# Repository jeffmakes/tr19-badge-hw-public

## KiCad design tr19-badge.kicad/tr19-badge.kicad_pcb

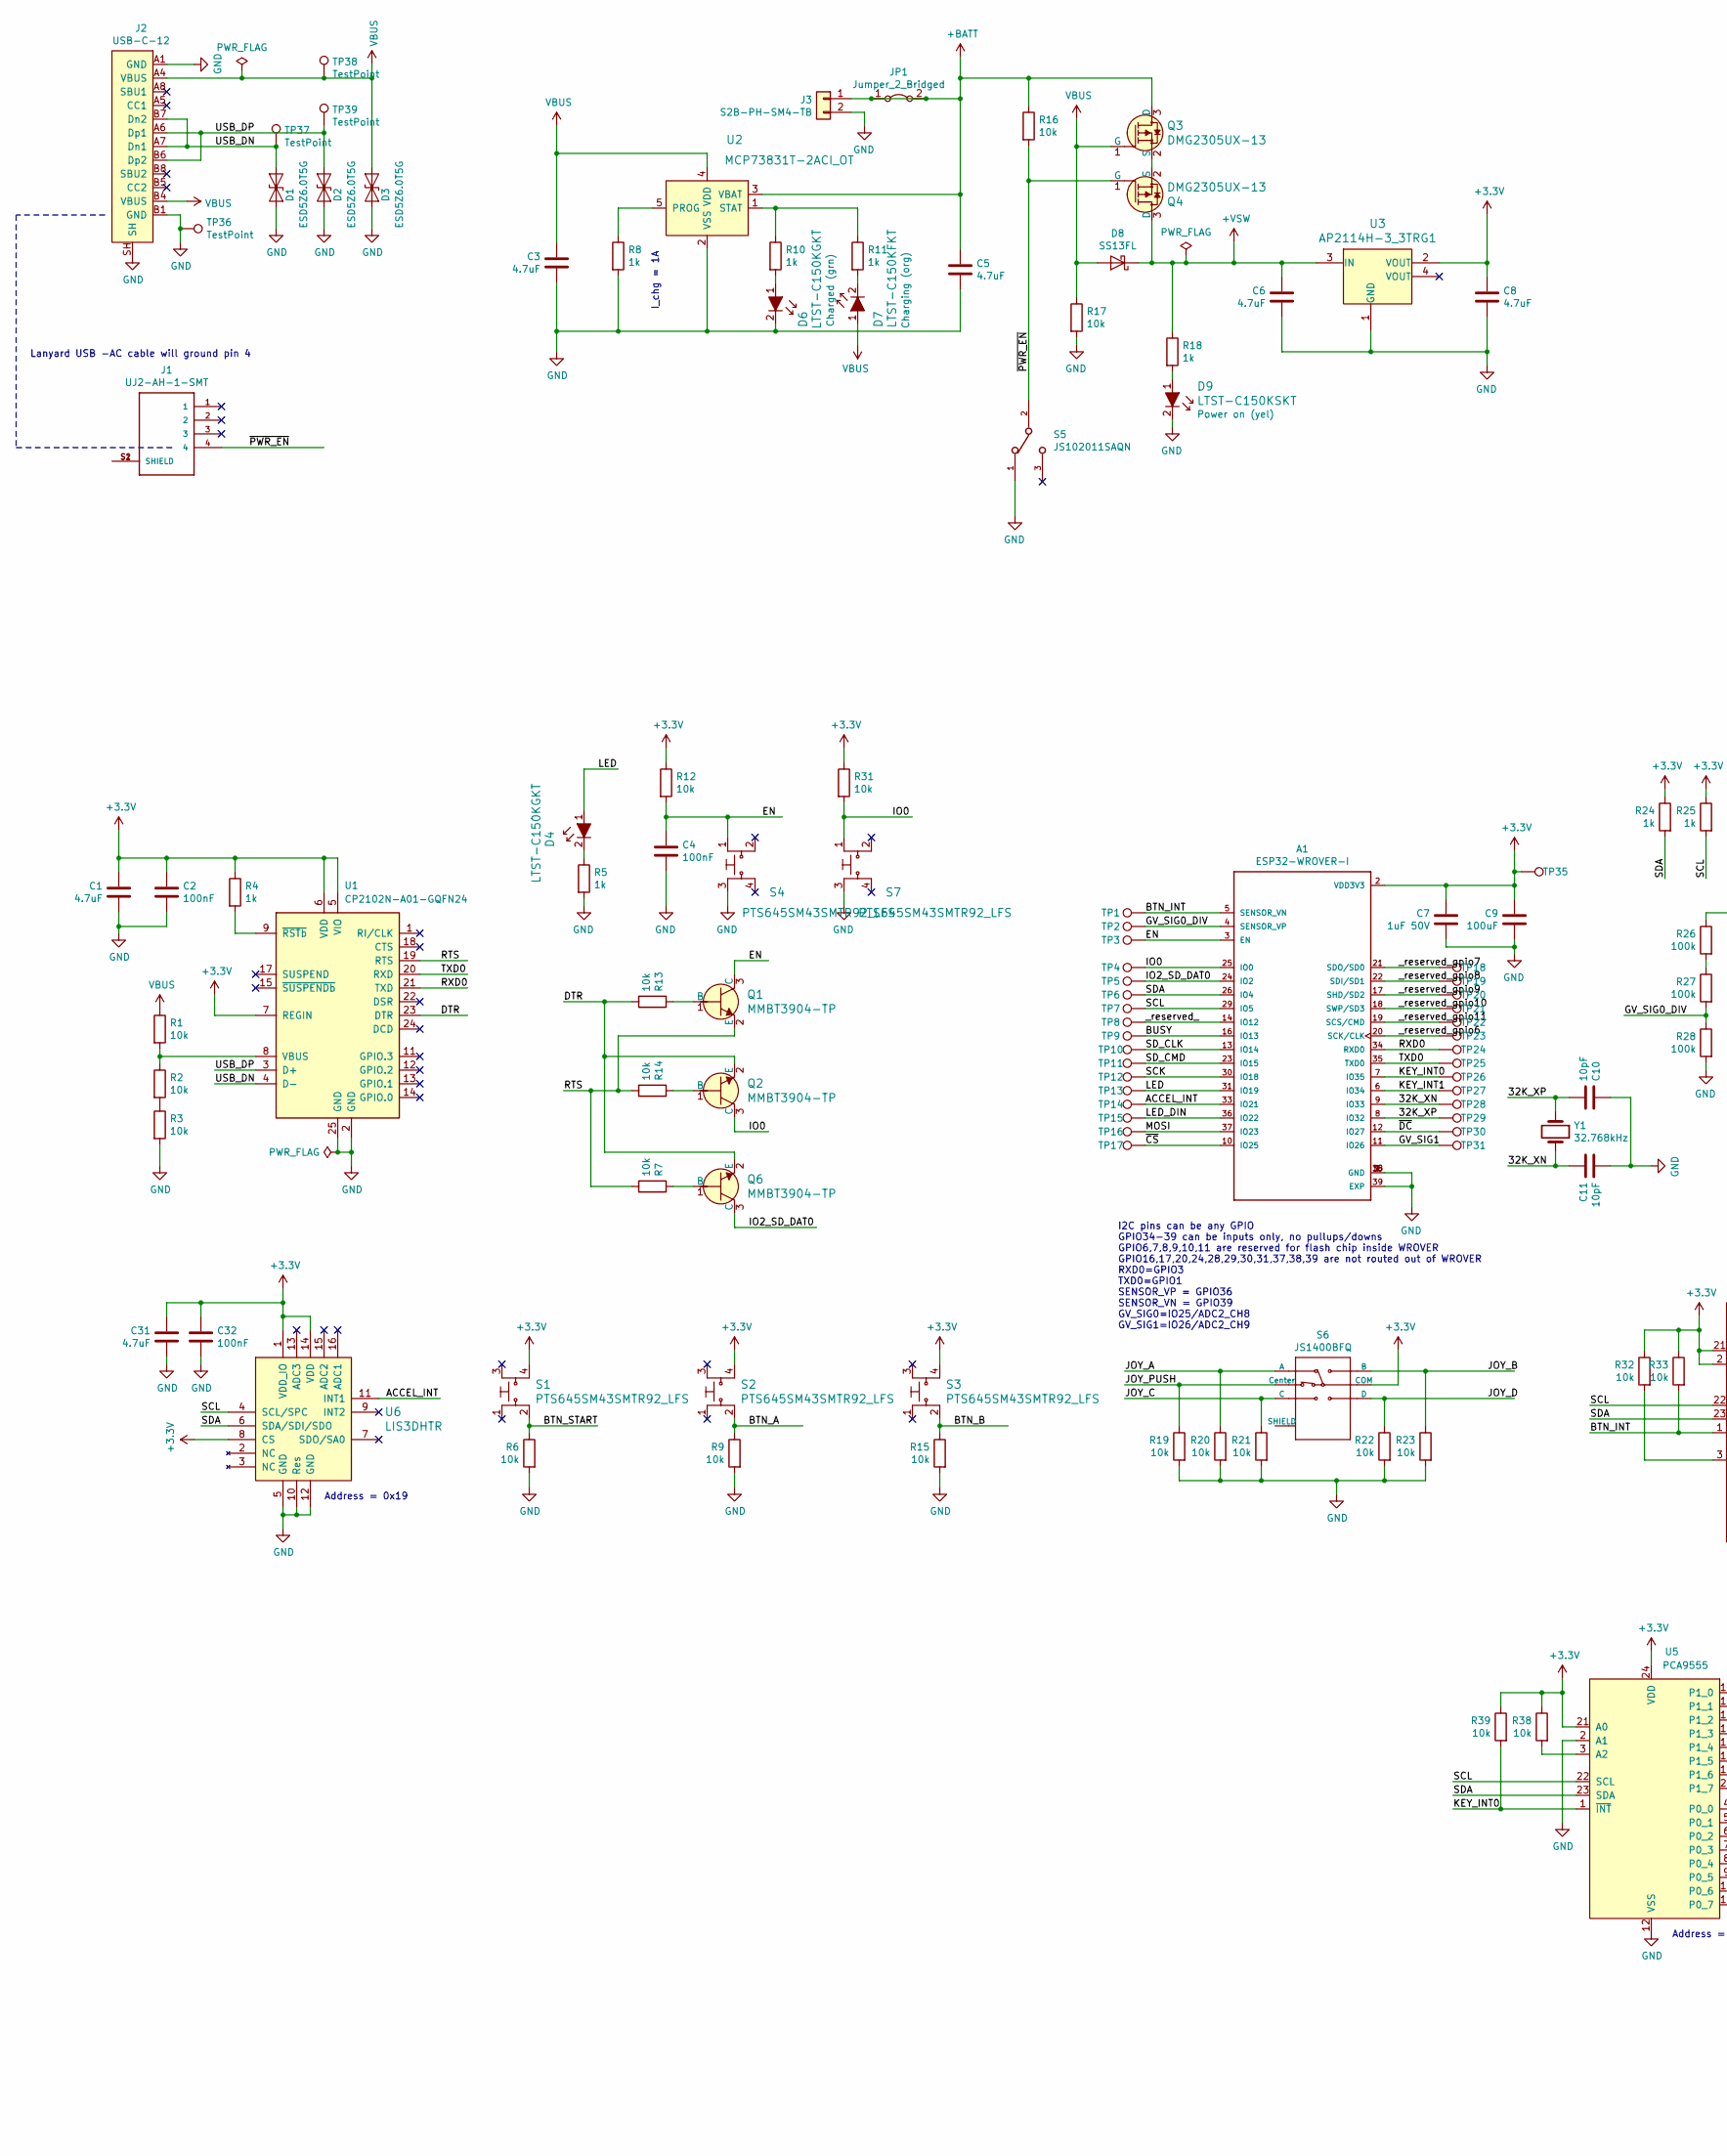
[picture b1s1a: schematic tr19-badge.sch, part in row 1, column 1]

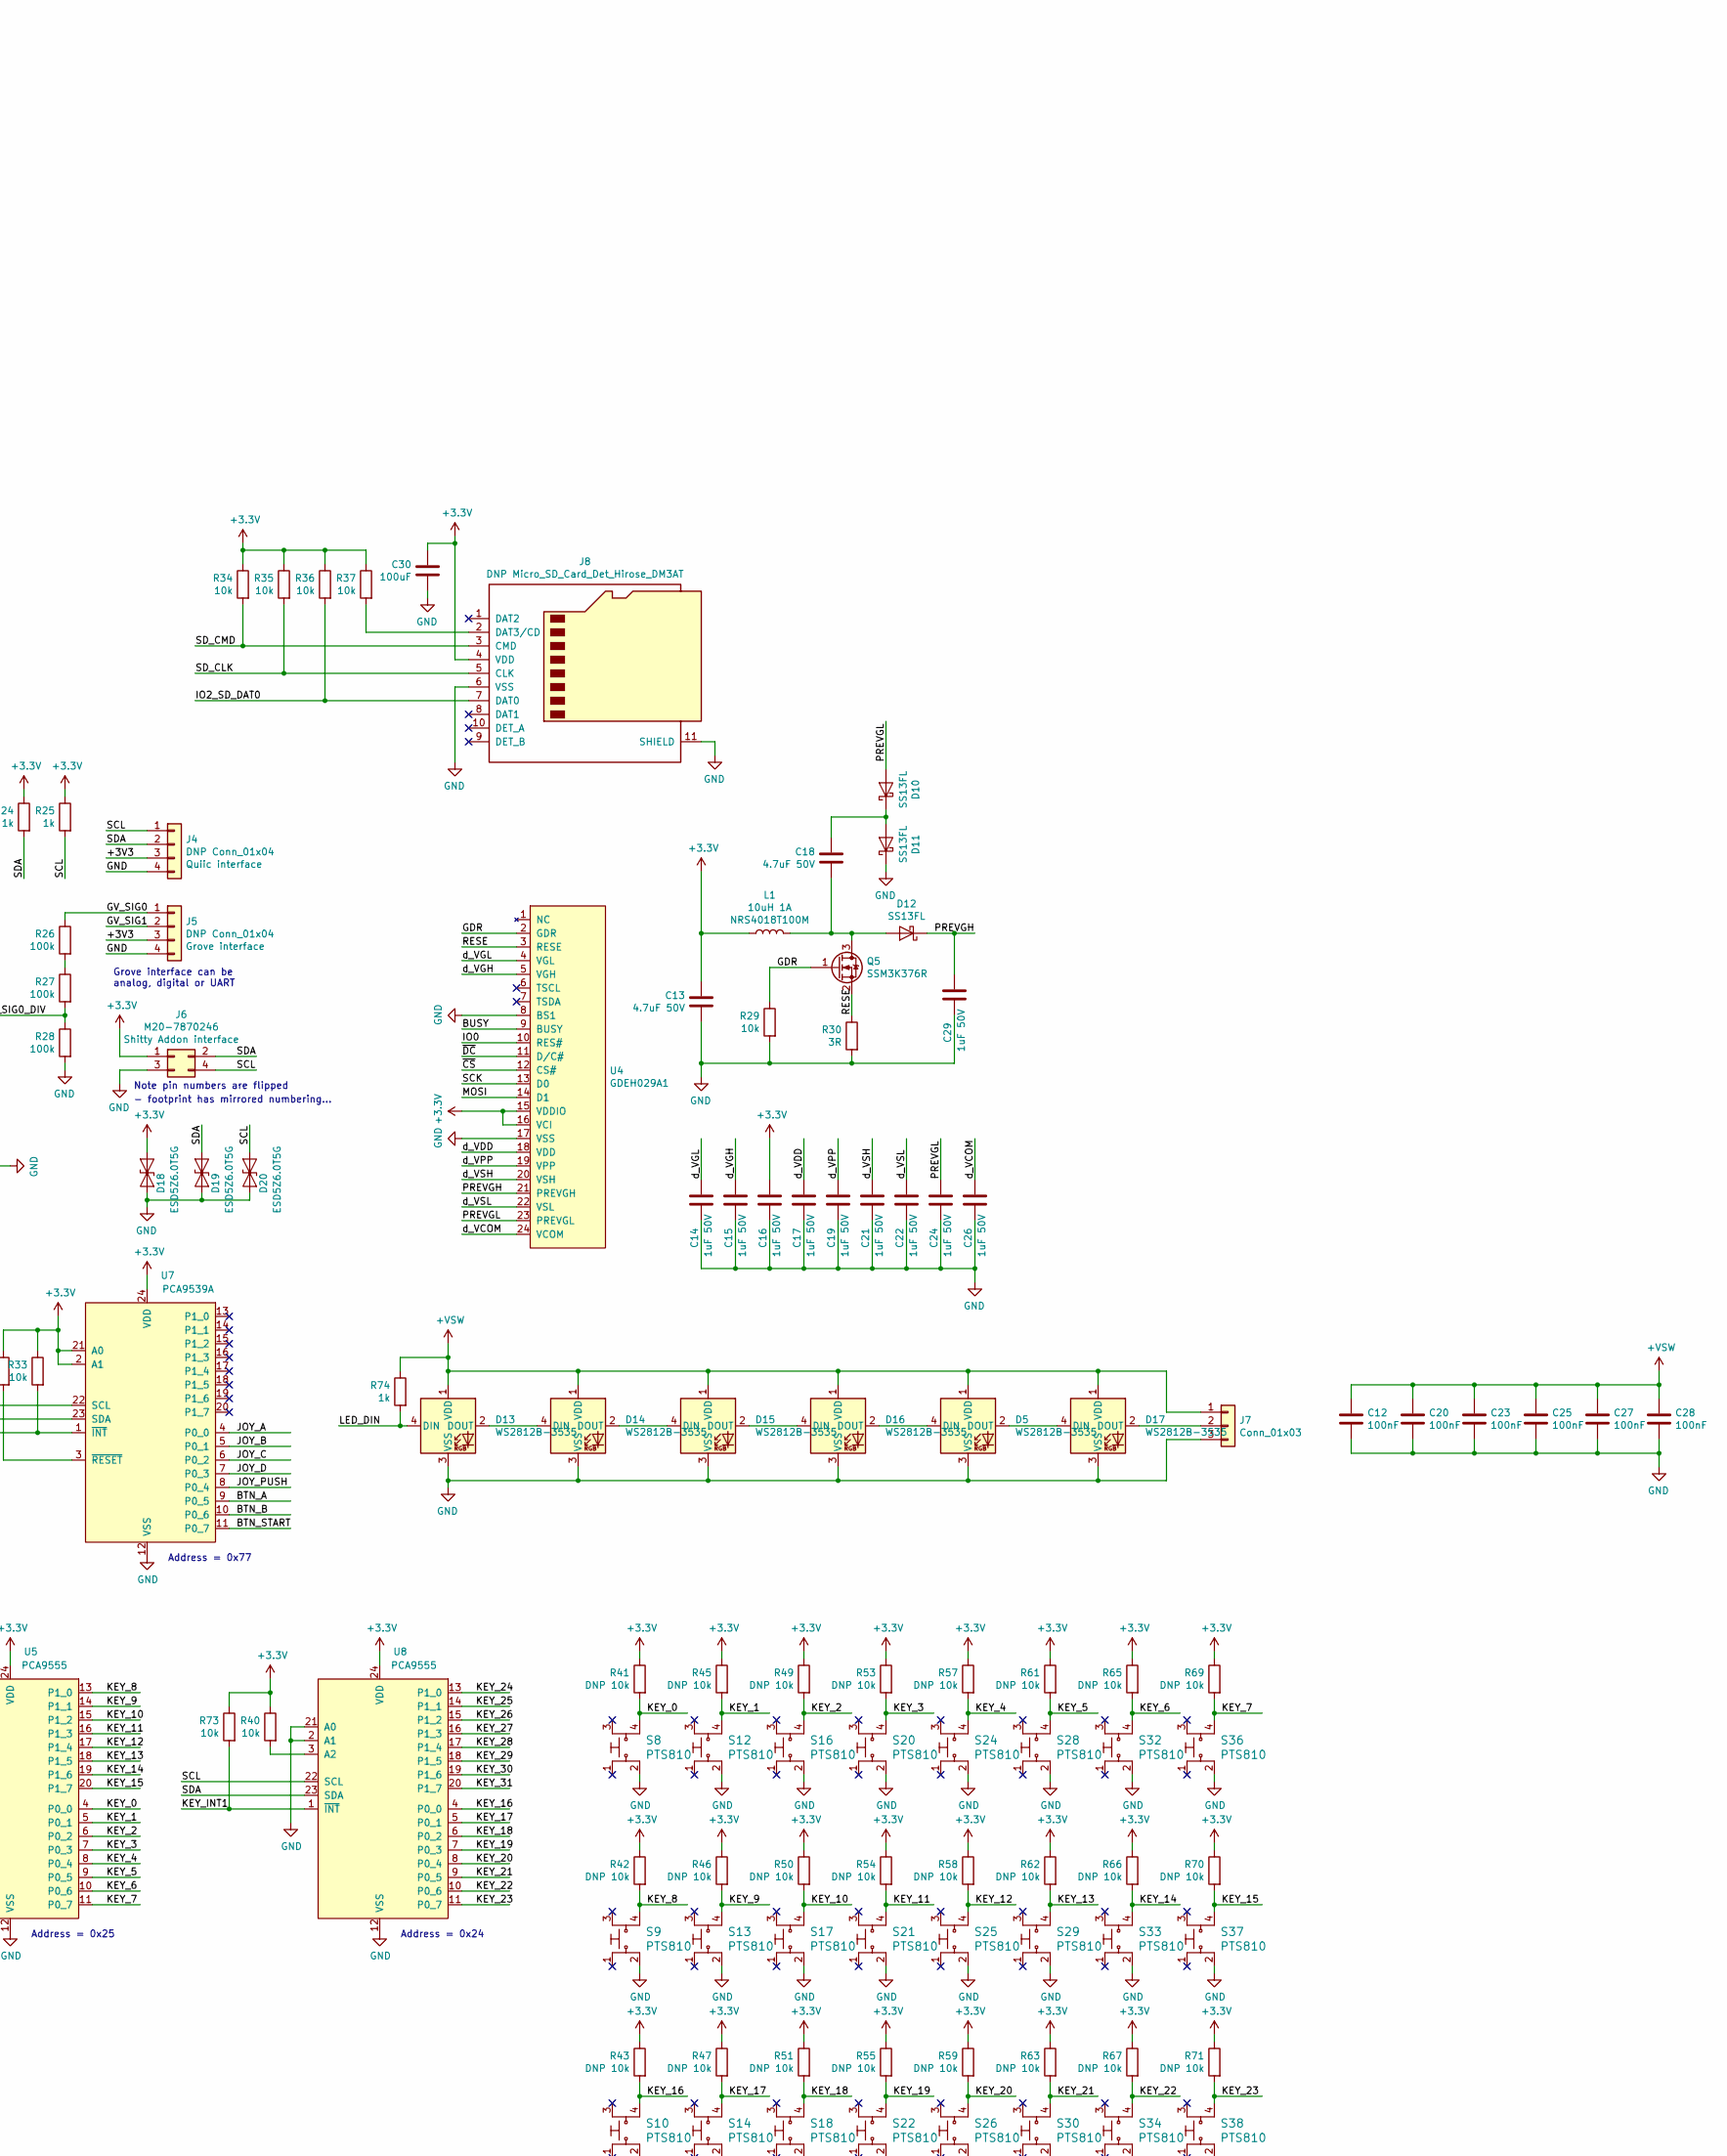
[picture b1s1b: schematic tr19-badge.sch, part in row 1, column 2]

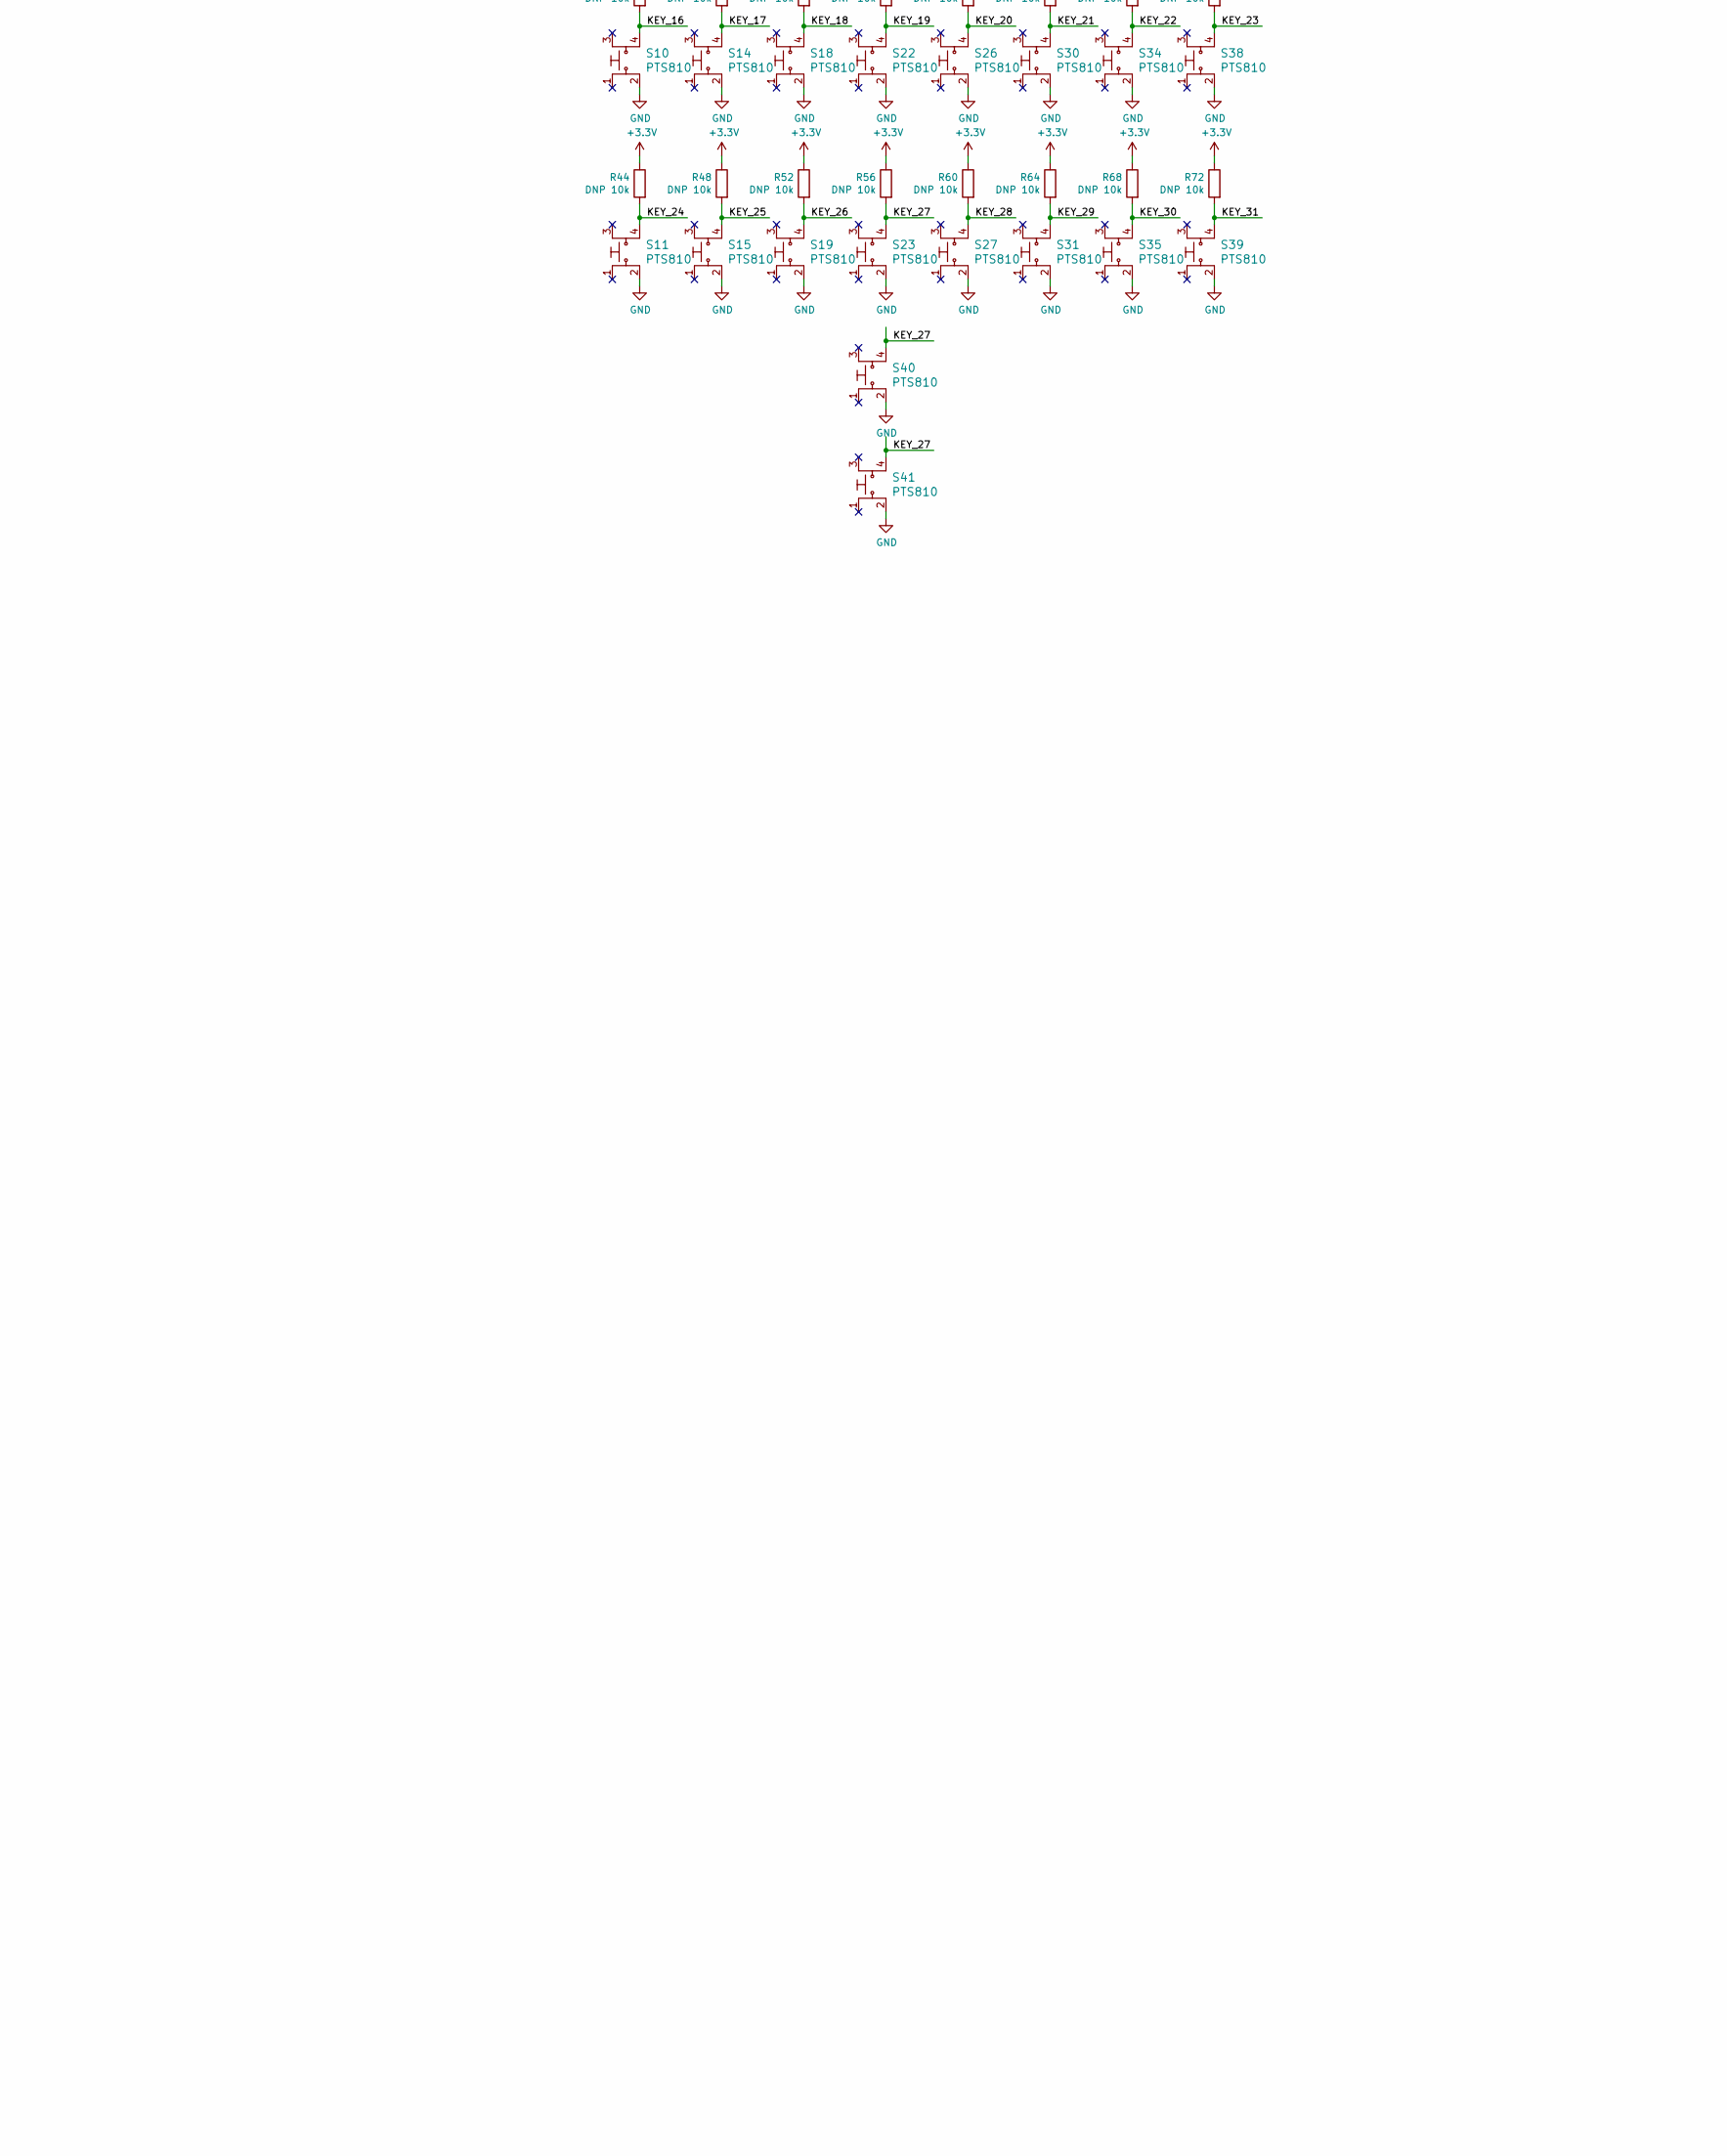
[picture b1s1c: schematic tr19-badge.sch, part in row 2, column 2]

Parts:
A1: ESP32-WROVER-I
C1, C3, C5, C6, C8, C31: 4.7uF; C_0603_1608Metric
C2, C4, C12, C20, C23, C25, C27, C28, C32: 100nF; C_0603_1608Metric
C7, C14, C15, C16, C17, C19, C21, C22, C24, C26, C29: 1uF 50V; C_0805_2012Metric
C9, C30: 100uF; C_1210_3225Metric
C10, C11: 10pF; C_0603_1608Metric
C13, C18: 4.7uF 50V; C_0805_2012Metric
D1, D2, D3, D18, D19, D20: ESD5Z6.0T5G; SOD-523-numbered-pads; MPN ESD5Z5.0VC
D4, D6: LTST-C150KGKT; 1206; MPN LTST-C150KGKT; Digi-Key_PN 160-1404-1-ND
D5, D13, D14, D15, D16, D17: WS2812B-3535; LED_SK6812MINI_PLCC4_3.5x3.5mm_P1.75mm_no_silk
D7: LTST-C150KFKT; 1206; MPN LTST-C150KSKT; Digi-Key_PN 160-1406-1-ND
D8, D10, D11, D12: SS13FL; D_SOD-123F
D9: LTST-C150KSKT; 1206; MPN LTST-C150KSKT; Digi-Key_PN 160-1406-1-ND
J1: UJ2-AH-1-SMT; jing-lcsc-C46400
J2: USB-C-12; jing-usb-c-lcsc-C167321
J3: S2B-PH-SM4-TB; JST_PH_S2B-PH-SM4-TB_1x02-1MP_P2.00mm_Horizontal
J4: DNP Conn_01x04; JST_SH_SM04B-SRSS-TB_1x04-1MP_P1.00mm_Horizontal
J5: DNP Conn_01x04; 1125R-SMT-4P
J6: M20-7870246; PinSocket_2x02_P2.54mm_Vertical_mirror_numbering
J7: Conn_01x03; PinHeader_1x03_P2.54mm_Vertical
J8: DNP Micro_SD_Card_Det_Hirose_DM3AT; microSD_HC_Hirose_DM3AT-SF-PEJM5
JP1: Jumper_2_Bridged; PinHeader_1x02_P2.54mm_Vertical
L1: 10uH 1A; L_Taiyo-Yuden_MD-5050; MPN NRS4018T100M
Q1, Q2, Q6: MMBT3904-TP; SOT-23-3; MPN MMBT3904-TP; Digi-Key_PN MMBT3904TPMSCT-ND
Q3, Q4: DMG2305UX-13; SOT-23-3; MPN DMG2305UX-13; Digi-Key_PN DMG2305UX-13DICT-ND
Q5: SSM3K376R; SOT-23
R1, R2, R3, R6, R7, R9, R12, R13, R14, R15, R16, R17, R19, R20, R21, R22, R23, R29, R31, R32, R33, R34, R35, R36, R37, R38, R39, R40, R73: 10k; R_0603_1608Metric
R4, R5, R8, R10, R11, R18, R24, R25, R74: 1k; R_0603_1608Metric
R26, R27, R28: 100k; R_0603_1608Metric
R30: 3R; R_0603_1608Metric
R41, R42, R43, R44, R45, R46, R47, R48, R49, R50, R51, R52, R53, R54, R55, R56, R57, R58, R59, R60, R61, R62, R63, R64, R65, R66, R67, R68, R69, R70, R71, R72: DNP 10k; R_0603_1608Metric
S1, S2, S3, S4, S7: PTS645SM43SMTR92_LFS; Switch_Tactile_SMD_6x6mm_PTS645; MPN PTS645SM43SMTR92 LFS; Digi-Key_PN CKN9112CT-ND
S5: JS102011SAQN; SW_JS102011SAQN
S6: JS1400BFQ; SW_JS1400BFQ-arrows
S8, S9, S10, S11, S12, S13, S14, S15, S16, S17, S18, S19, S20, S21, S22, S23, S24, S25, S26, S27, S28, S29, S30, S31, S32, S33, S34, S35, S36, S37, S38, S39, S40, S41: PTS810; PTS-810; MPN PTS645SM43SMTR92 LFS; Digi-Key_PN CKN9112CT-ND
TP1, TP2, TP3, TP4, TP5, TP6, TP7, TP8, TP9, TP10, TP11, TP12, TP13, TP14, TP15, TP16, TP17, TP18, TP19, TP20, TP21, TP22, TP23, TP24, TP25, TP26, TP27, TP28, TP29, TP30, TP31, TP35: test-pad-1.4-TH
TP36, TP37, TP38, TP39: TestPoint; test-pad-1.4-TH
U1: CP2102N-A01-GQFN24; QFN-24-1EP_4x4mm_P0.5mm_EP2.6x2.6mm
U2: MCP73831T-2ACI_OT; SOT-753; MPN MCP73831T-2ACI/OT; Digi-Key_PN MCP73831T-2ACI/OTCT-ND
U3: AP2114H-3_3TRG1; SOT-223; MPN AP2114H-3.3TRG1; Digi-Key_PN AP2114H-3.3TRG1DICT-ND
U4: GDEH029A1
U5, U8: PCA9555; TSSOP-24_4.4x7.8mm_P0.65mm
U6: LIS3DHTR; VFLGA-16_3x3mm; MPN LIS3DHTR; Digi-Key_PN 497-10613-1-ND
U7: PCA9539A; TSSOP-24_4.4x7.8mm_P0.65mm
Y1: 32.768kHz; Crystal_SMD_3215-2Pin_3.2x1.5mm; MPN SSP-T7-F

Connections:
+BATT: C5.1, J3.1, JP1.1 (A), JP1.2 (B), Q3.3 (D), R16.1, U2.3 (VBAT)
+VSW: C6.1, C12.1, C20.1, C23.1, C25.1, C27.1, C28.1, D5.1 (VDD), D8.1 (K), D13.1 (VDD), D14.1 (VDD), D15.1 (VDD), D16.1 (VDD), D17.1 (VDD), J7.1, Q4.3 (D), R18.1, R74.1, U3.3 (IN)
/32K_XN: A1.9 (IO33), C11.1, TP28.1, Y1.2
/32K_XP: A1.8 (IO32), C10.2, TP29.1, Y1.1
/ACCEL_INT: A1.33 (IO21), TP14.1, U6.11 (INT1)
/BTN_A: R9.1, S2.2, U7.9 (P0_5)
/BTN_B: R15.1, S3.2, U7.10 (P0_6)
/BTN_INT: A1.5 (SENSOR_VN), R33.2, TP1.1, U7.1 (~INT~)
/BTN_START: R6.1, S1.2, U7.11 (P0_7)
/BUSY: A1.16 (IO13), TP9.1, U4.9 (BUSY)
/DTR: Q2.2 (E), Q6.2 (E), R13.2, U1.23 (DTR)
/EN: A1.3 (EN), C4.1, Q1.3 (C), R12.2, S4.1, TP3.1
/GDR: Q5.1 (G), R29.1, U4.2 (GDR)
/GV_SIG0: J5.1, R26.1
/GV_SIG0_DIV: A1.4 (SENSOR_VP), R27.2, R28.1, TP2.1
/GV_SIG1: A1.11 (IO26), J5.2, TP31.1
/IO0: A1.25 (IO0), Q2.3 (C), R31.2, S7.1, TP4.1, U4.10 (RES#)
/IO2_SD_DAT0: A1.24 (IO2), J8.7 (DAT0), Q6.3 (C), R36.2, TP5.1
/JOY_A: R20.1, S6.1 (A), U7.4 (P0_0)
/JOY_B: R23.1, S6.4 (B), U7.5 (P0_1)
/JOY_C: R21.1, S6.3 (C), U7.6 (P0_2)
/JOY_D: R22.1, S6.6 (D), U7.7 (P0_3)
/JOY_PUSH: R19.1, S6.2 (Center), U7.8 (P0_4)
/KEY_0: R41.2, S8.4, U5.4 (P0_0)
/KEY_1: R45.2, S12.4, U5.5 (P0_1)
/KEY_2: R49.2, S16.4, U5.6 (P0_2)
/KEY_3: R53.2, S20.4, U5.7 (P0_3)
/KEY_4: R57.2, S24.4, U5.8 (P0_4)
/KEY_5: R61.2, S28.4, U5.9 (P0_5)
/KEY_6: R65.2, S32.4, U5.10 (P0_6)
/KEY_7: R69.2, S36.4, U5.11 (P0_7)
/KEY_8: R42.2, S9.4, U5.13 (P1_0)
/KEY_9: R46.2, S13.4, U5.14 (P1_1)
/KEY_10: R50.2, S17.4, U5.15 (P1_2)
/KEY_11: R54.2, S21.4, U5.16 (P1_3)
/KEY_12: R58.2, S25.4, U5.17 (P1_4)
/KEY_13: R62.2, S29.4, U5.18 (P1_5)
/KEY_14: R66.2, S33.4, U5.19 (P1_6)
/KEY_15: R70.2, S37.4, U5.20 (P1_7)
/KEY_16: R43.2, S10.4, U8.4 (P0_0)
/KEY_17: R47.2, S14.4, U8.5 (P0_1)
/KEY_18: R51.2, S18.4, U8.6 (P0_2)
/KEY_19: R55.2, S22.4, U8.7 (P0_3)
/KEY_20: R59.2, S26.4, U8.8 (P0_4)
/KEY_21: R63.2, S30.4, U8.9 (P0_5)
/KEY_22: R67.2, S34.4, U8.10 (P0_6)
/KEY_23: R71.2, S38.4, U8.11 (P0_7)
/KEY_24: R44.2, S11.4, U8.13 (P1_0)
/KEY_25: R48.2, S15.4, U8.14 (P1_1)
/KEY_26: R52.2, S19.4, U8.15 (P1_2)
/KEY_27: R56.2, S23.4, S40.4, S41.4, U8.16 (P1_3)
/KEY_28: R60.2, S27.4, U8.17 (P1_4)
/KEY_29: R64.2, S31.4, U8.18 (P1_5)
/KEY_30: R68.2, S35.4, U8.19 (P1_6)
/KEY_31: R72.2, S39.4, U8.20 (P1_7)
/KEY_INT0: A1.7 (IO35), R39.2, TP26.1, U5.1 (~INT~)
/KEY_INT1: A1.6 (IO34), R73.2, TP27.1, U8.1 (~INT~)
/LED: A1.31 (IO19), D4.1, TP13.1
/LED_DIN: A1.36 (IO22), D13.4 (DIN), R74.2, TP15.1
/MOSI: A1.37 (IO23), TP16.1, U4.14 (D1)
/PREVGH: C29.2, D12.1 (K), U4.21 (PREVGH)
/PREVGL: C24.2, D10.2 (A), U4.23 (PREVGL)
/RESE: Q5.2 (S), R30.1, U4.3 (RESE)
/RTS: Q1.2 (E), R7.2, R14.2, U1.19 (RTS)
/RXD0: A1.34 (RXD0), TP24.1, U1.21 (TXD)
/SCK: A1.30 (IO18), TP12.1, U4.13 (D0)
/SCL: A1.29 (IO5), D20.1 (A1), J4.1, J6.4, R25.2, TP7.1, U5.22 (SCL), U6.4 (SCL/SPC), U7.22 (SCL), U8.22 (SCL)
/SDA: A1.26 (IO4), D19.1 (A1), J4.2, J6.2, R24.2, TP6.1, U5.23 (SDA), U6.6 (SDA/SDI/SDO), U7.23 (SDA), U8.23 (SDA)
/SD_CLK: A1.13 (IO14), J8.5 (CLK), R35.2, TP10.1
/SD_CMD: A1.23 (IO15), J8.3 (CMD), R34.2, TP11.1
/TXD0: A1.35 (TXD0), TP25.1, U1.20 (RXD)
/USB_DN: D1.1 (A1), J2.A7 (Dn1), J2.B7 (Dn2), TP37.1, U1.4 (D-)
/USB_DP: D2.1 (A1), J2.A6 (Dp1), J2.B6 (Dp2), TP39.1, U1.3 (D+)
/_reserved_: A1.14 (IO12), TP8.1
/_reserved_gpio6: A1.20 (SCK/CLK), TP23.1
/_reserved_gpio7: A1.21 (SDO/SD0), TP18.1
/_reserved_gpio8: A1.22 (SDI/SD1), TP19.1
/_reserved_gpio9: A1.17 (SHD/SD2), TP20.1
/_reserved_gpio10: A1.18 (SWP/SD3), TP21.1
/_reserved_gpio11: A1.19 (SCS/CMD), TP22.1
/d_VCOM: C26.2, U4.24 (VCOM)
/d_VDD: C17.2, U4.18 (VDD)
/d_VGH: C15.2, U4.5 (VGH)
/d_VGL: C14.2, U4.4 (VGL)
/d_VPP: C19.2, U4.19 (VPP)
/d_VSH: C21.2, U4.20 (VSH)
/d_VSL: C22.2, U4.22 (VSL)
/~CS~: A1.10 (IO25), TP17.1, U4.12 (CS#)
/~DC~: A1.12 (IO27), TP30.1, U4.11 (D/C#)
/~PWR_EN~: J1.4, Q4.1 (G), R16.2, S5.2
GND: A1.1 (GND), A1.15 (GND), A1.38 (GND), A1.39 (EXP), C1.2, C2.2, C3.2, C4.2, C5.2, C6.2, C7.2, C8.2, C9.2, C10.1, C11.2, C12.2, C13.2, C14.1, C15.1, C16.1, C17.1, C19.1, C20.2, C21.1, C22.1, C23.2, C24.1, C25.2, C26.1, C27.2, C28.2, C29.1, C30.2, C31.2, C32.2, D1.2 (A2), D2.2 (A2), D3.2 (A2), D5.3 (VSS), D6.2, D9.2, D11.1 (K), D13.3 (VSS), D14.3 (VSS), D15.3 (VSS), D16.3 (VSS), D17.3 (VSS), D18.2 (A2), D19.2 (A2), D20.2 (A2), J2.A1 (GND), J2.B1 (GND), J2.SH, J3.2, J4.4, J5.4, J6.3, J7.3, J8.6 (VSS), J8.11 (SHIELD), R3.2, R5.2, R6.2, R8.2, R9.2, R15.2, R17.2, R19.2, R20.2, R21.2, R22.2, R23.2, R28.2, R29.2, R30.2, S4.3, S5.1, S7.3, S8.2, S9.2, S10.2, S11.2, S12.2, S13.2, S14.2, S15.2, S16.2, S17.2, S18.2, S19.2, S20.2, S21.2, S22.2, S23.2, S24.2, S25.2, S26.2, S27.2, S28.2, S29.2, S30.2, S31.2, S32.2, S33.2, S34.2, S35.2, S36.2, S37.2, S38.2, S39.2, S40.2, S41.2, TP36.1, U1.2 (GND), U1.25 (GND), U2.2 (VSS), U3.1 (GND), U4.8 (BS1), U4.17 (VSS), U5.2 (A1), U5.12 (VSS), U6.5 (GND), U6.10 (Res), U6.12 (GND), U7.12 (VSS), U8.2 (A1), U8.12 (VSS), U8.21 (A0)
unnamed: C18.1, D10.1 (K), D11.2 (A)
unnamed: C18.2, D12.2 (A), L1.2, Q5.3 (D)
unnamed: D4.2, R5.1
unnamed: D6.1, R10.2
unnamed: D7.2, R11.2
unnamed: D9.1, R18.2
unnamed: D13.2 (DOUT), D14.4 (DIN)
unnamed: D14.2 (DOUT), D15.4 (DIN)
unnamed: D15.2 (DOUT), D16.4 (DIN)
unnamed: D5.4 (DIN), D16.2 (DOUT)
unnamed: D17.2 (DOUT), J7.2
unnamed: D5.2 (DOUT), D17.4 (DIN)
unnamed: J1.S1 (SHIELD), J1.S2 (SHIELD)
unnamed: J8.2 (DAT3/CD), R37.2
unnamed: Q1.1 (B), R13.1
unnamed: Q2.1 (B), R14.1
unnamed: Q3.2 (S), Q4.2 (S)
unnamed: Q6.1 (B), R7.1
unnamed: R1.2, R2.1, U1.8 (VBUS)
unnamed: R2.2, R3.1
unnamed: R4.2, U1.9 (~RSTb)
unnamed: R8.1, U2.5 (PROG)
unnamed: R10.1, R11.1, U2.1 (STAT)
unnamed: R26.2, R27.1
unnamed: R32.2, U7.3 (~RESET~)
unnamed: R38.2, U5.3 (A2)
unnamed: R40.2, U8.3 (A2)
unnamed: S6.SH1 (SHIELD), S6.SH2 (SHIELD)
VBUS: C3.1, D3.1 (A1), D7.1, D8.2 (A), J2.A4 (VBUS), J2.B4 (VBUS), Q3.1 (G), R1.1, R17.1, TP38.1, U2.4 (VDD)

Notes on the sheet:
I_chg = 1A
Lanyard USB -AC cable will ground pin 4
Grove interface can be analog, digital or UART
I2C pins can be any GPIO GPIO34-39 can be inputs only, no pullups/downs GPIO6,7,8,9,10,11 are reserved for flash chip inside WROVER GPIO16,17,20,24,28,29,30,31,37,38,39 are not routed out of WROVER RXD0=GPIO3 TXD0=GPIO1 SENSOR_VP = GPIO36 SENSOR_VN = GPIO39 GV_SIG0=IO25/ADC2_CH8 GV_SIG1=IO26/ADC2_C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
Note pin numbers are flipped
- footprint has mirrored numbering...
Address = 0x77
Address = 0x19
Address = 0x25
Address = 0x24

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
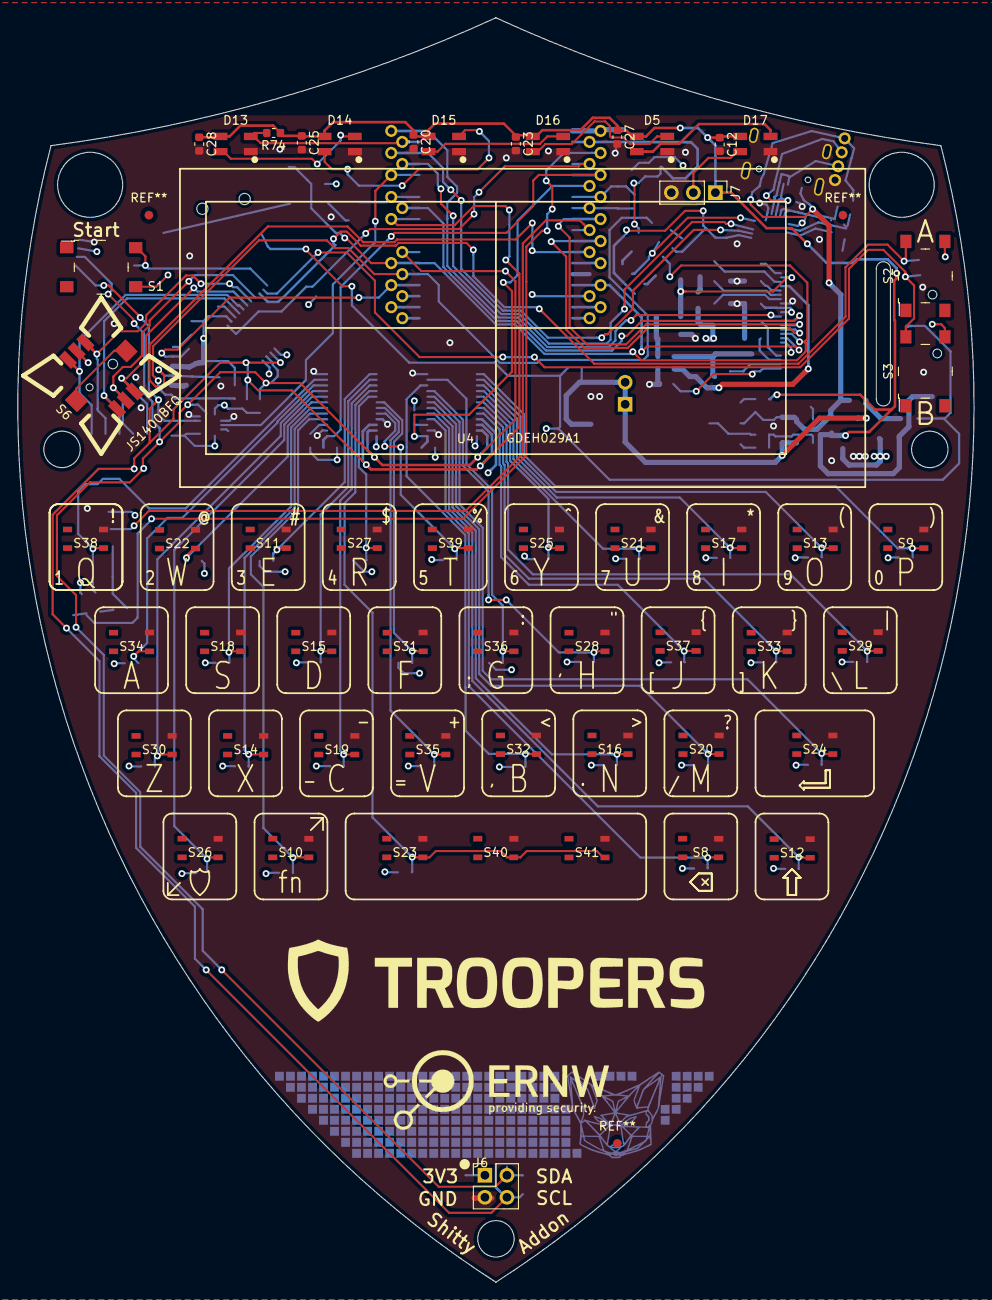
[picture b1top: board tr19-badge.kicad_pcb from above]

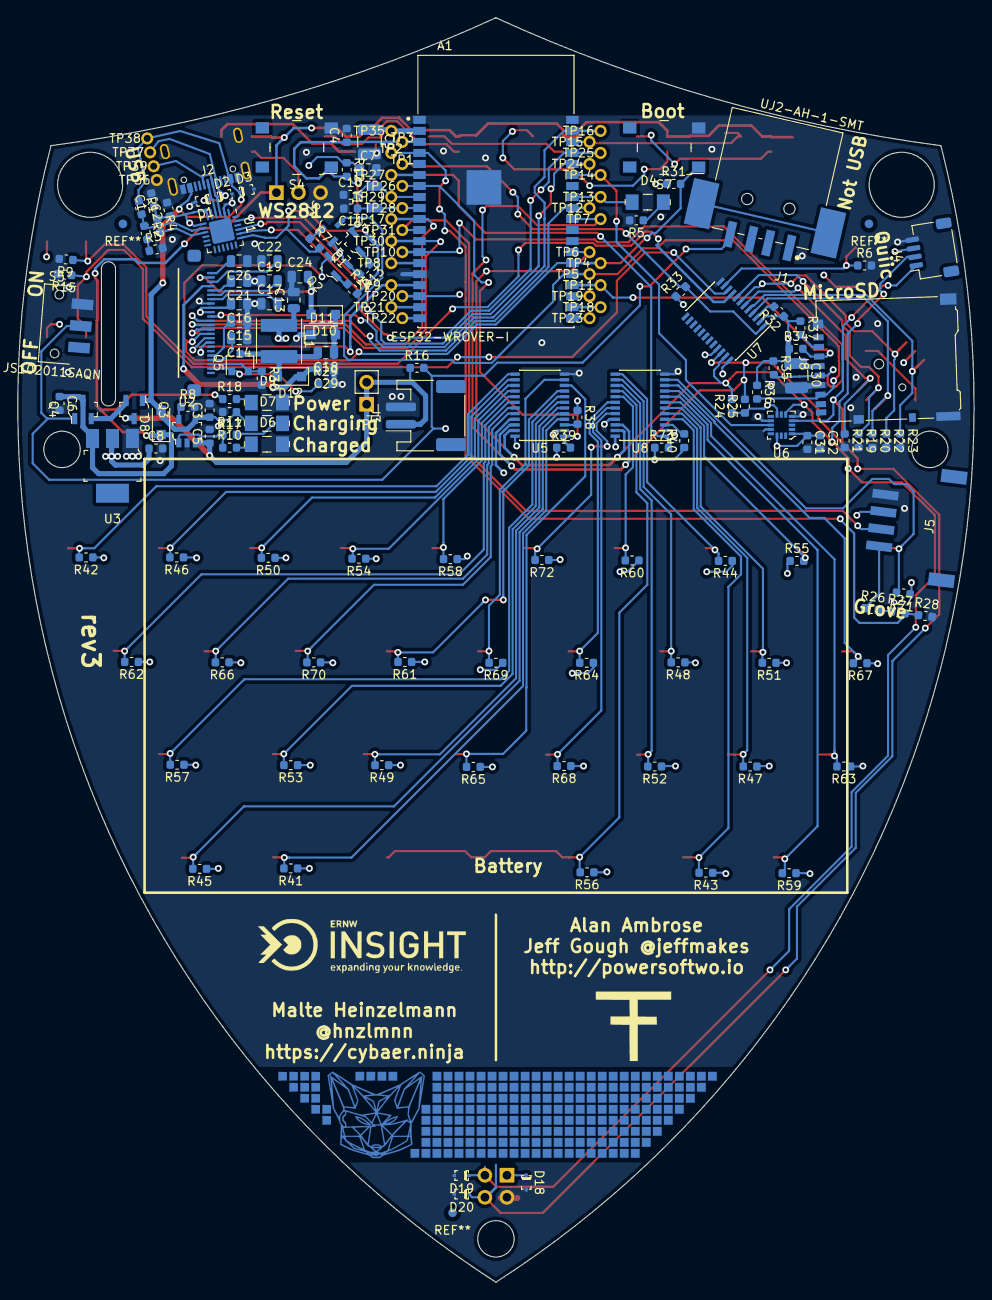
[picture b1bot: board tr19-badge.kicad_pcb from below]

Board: 4 copper layers, 110.2 x 145.8 mm, 234 parts (177 on the bottom side), 121 nets.

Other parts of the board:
Ref**: Val**; poft-icon-8mm
Ref**#2: Val**; fuccs-soldering
Ref**#3: Val**; trroopers-48mm
Ref**#4: Val**; ernw-26mm
Ref**#5: Val**; ernw-insight-24mm
